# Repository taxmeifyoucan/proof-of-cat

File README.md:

**[ENG](README.md) | [CAT](README_cat.md)**

# Proof-of-Cat: Cat as an entropy generator

Proof-of-Cat is a novel approach to generating randomness for cryptographic systems, utilizing the inherent unpredictability and entropy of domestic felines, also known as cats.

To learn more, read the **[CatPaper](./proofofcat.pdf)** and check the **Catropy [docs](./docs.md)**. 

## Catropy

_Catropy_ is a CRNG (Cat Random Number Generator) designed as an implementation of Proof-of-Cat. Research and development of this device was intented for participation in [Ethereum KZG Ceremony](https://github.com/ethereum/kzg-ceremony) and supported by EF grant. Read the [blog](./blog.md) about how Catropy uses cats to secure Ethereum.

It's a basically toy which can generate randomness from its movement. The circuit board is a microcontroller with wifi and battery which enables to use the device fully remotely. To learn more about hardware design and usage, look into the [documentation](./docs.md). 

The toy is not just a circuit board. It comes in hand-made knitted ball which protects the electronics and provides soft experience. It was demonstrated that it works well not just with [cats](https://twitter.com/i/status/1632706164231118848), [but also core devs](https://twitter.com/liamihorne/status/1617974952413761536). Various versions and color combinations are available. Check example pictures below. 

Device can be used to contribute to the KZG Ceremony but it is not its sole purpose. The Catropy software enables you to use it for generating entropy for anything which needs it. But the device is general purpose and you can reprogram it to utilize the microctroller however you want. For example, another use case being developed is for using the device for medical diagnostic of patients based on tracking their movement and its changes. 

## Get a Catropy device

Catropy was designed as an open-source device with no profit incentives. You can build the device by yourself but if you would like purchase one, you can do it by donating to a [cat shelter in Catalonia](https://www.eljardinetdelsgats.org). Based on donation of minumum 0.02ETH, we will reward you with a fully featured Catropy toy. 

And if you are a member of Protocol Guild, the toy completely on us! 

### Donation

Donations are handled by us, converted to fiat and physically donated to [El Jardinet dels Gats](https://www.eljardinetdelsgats.org), a non-profit helping cats which was also involved testing the Catropy toy. In case we receive high number of donations (0.5ETH+), it will be split between Jardinet and another [local organization](https://www.degats.org/) with multiple colonies. The official donation address is catropy.eth (0x543cbBD2bf6f6eC71254E75b7FEAbb222B143343). All funds on this address will be donated to help with expenses in the shelter - food, materials, veterinary checks, treatement and vaccinations. 

### Shipping 

You can pickup Catropy personally during **EthPrague** conference or rest of the year in [Paralelní Polis](https://goo.gl/maps/rJfCFSxNbkSRXrLw9) or in Barcelona. 

Otherwise we can ship it to your address. Just add shipping fee to your donation, you can use a [shipping estimate calculator](https://coolparcel.com/). (0.5kg package, shipping from Czech republic, 17001). Feel free to reach out if you are not sure, we can ship it first and let you know the exact cost. 

### How to

Step by step, this is how you get your device: 

- Donate minimum of 0.02ETH (around 30EUR) to catropy.eth or 0x543cbBD2bf6f6eC71254E75b7FEAbb222B143343. You can use mainnet, Arbitrum, Optimism, Polygon, Gnosis chain or Aztec (zk.money, address is @catropy). For donating over other chains, reach out to us. 
- Choose a color combination. Balls come in various colors, we prepared gray with colorful ETH logo, pink with white logo and blue with yellow. Check pictures below and more in [assets directory](https://github.com/taxmeifyoucan/proof-of-cat/tree/gh-pages/src/assets). If you wish your own color combination, feel free to write us but note it might take few extra days before shipping. 
- Send us an email to meow@proofof.cat with your shipping details (your address or pickup option), chosen color and sign it with the address you sent donation from. Signing message with a wallet is easy, you can use a tool like [MyCrypto](https://app.mycrypto.com/sign-message). If you are a Protocol Guild member, sign it using your address PG or just contact us to verify it's really you. 
- Embrace the chaos 

## Contact

For support, orders and any kind of questions, please contact us at meow@proofof.cat

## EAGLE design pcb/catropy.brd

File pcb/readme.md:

# Catropy PCB

Schematics for the Catropy board. Files in this directory contain all sources for Catropy hardware and can be opened using Eagle or similar software.

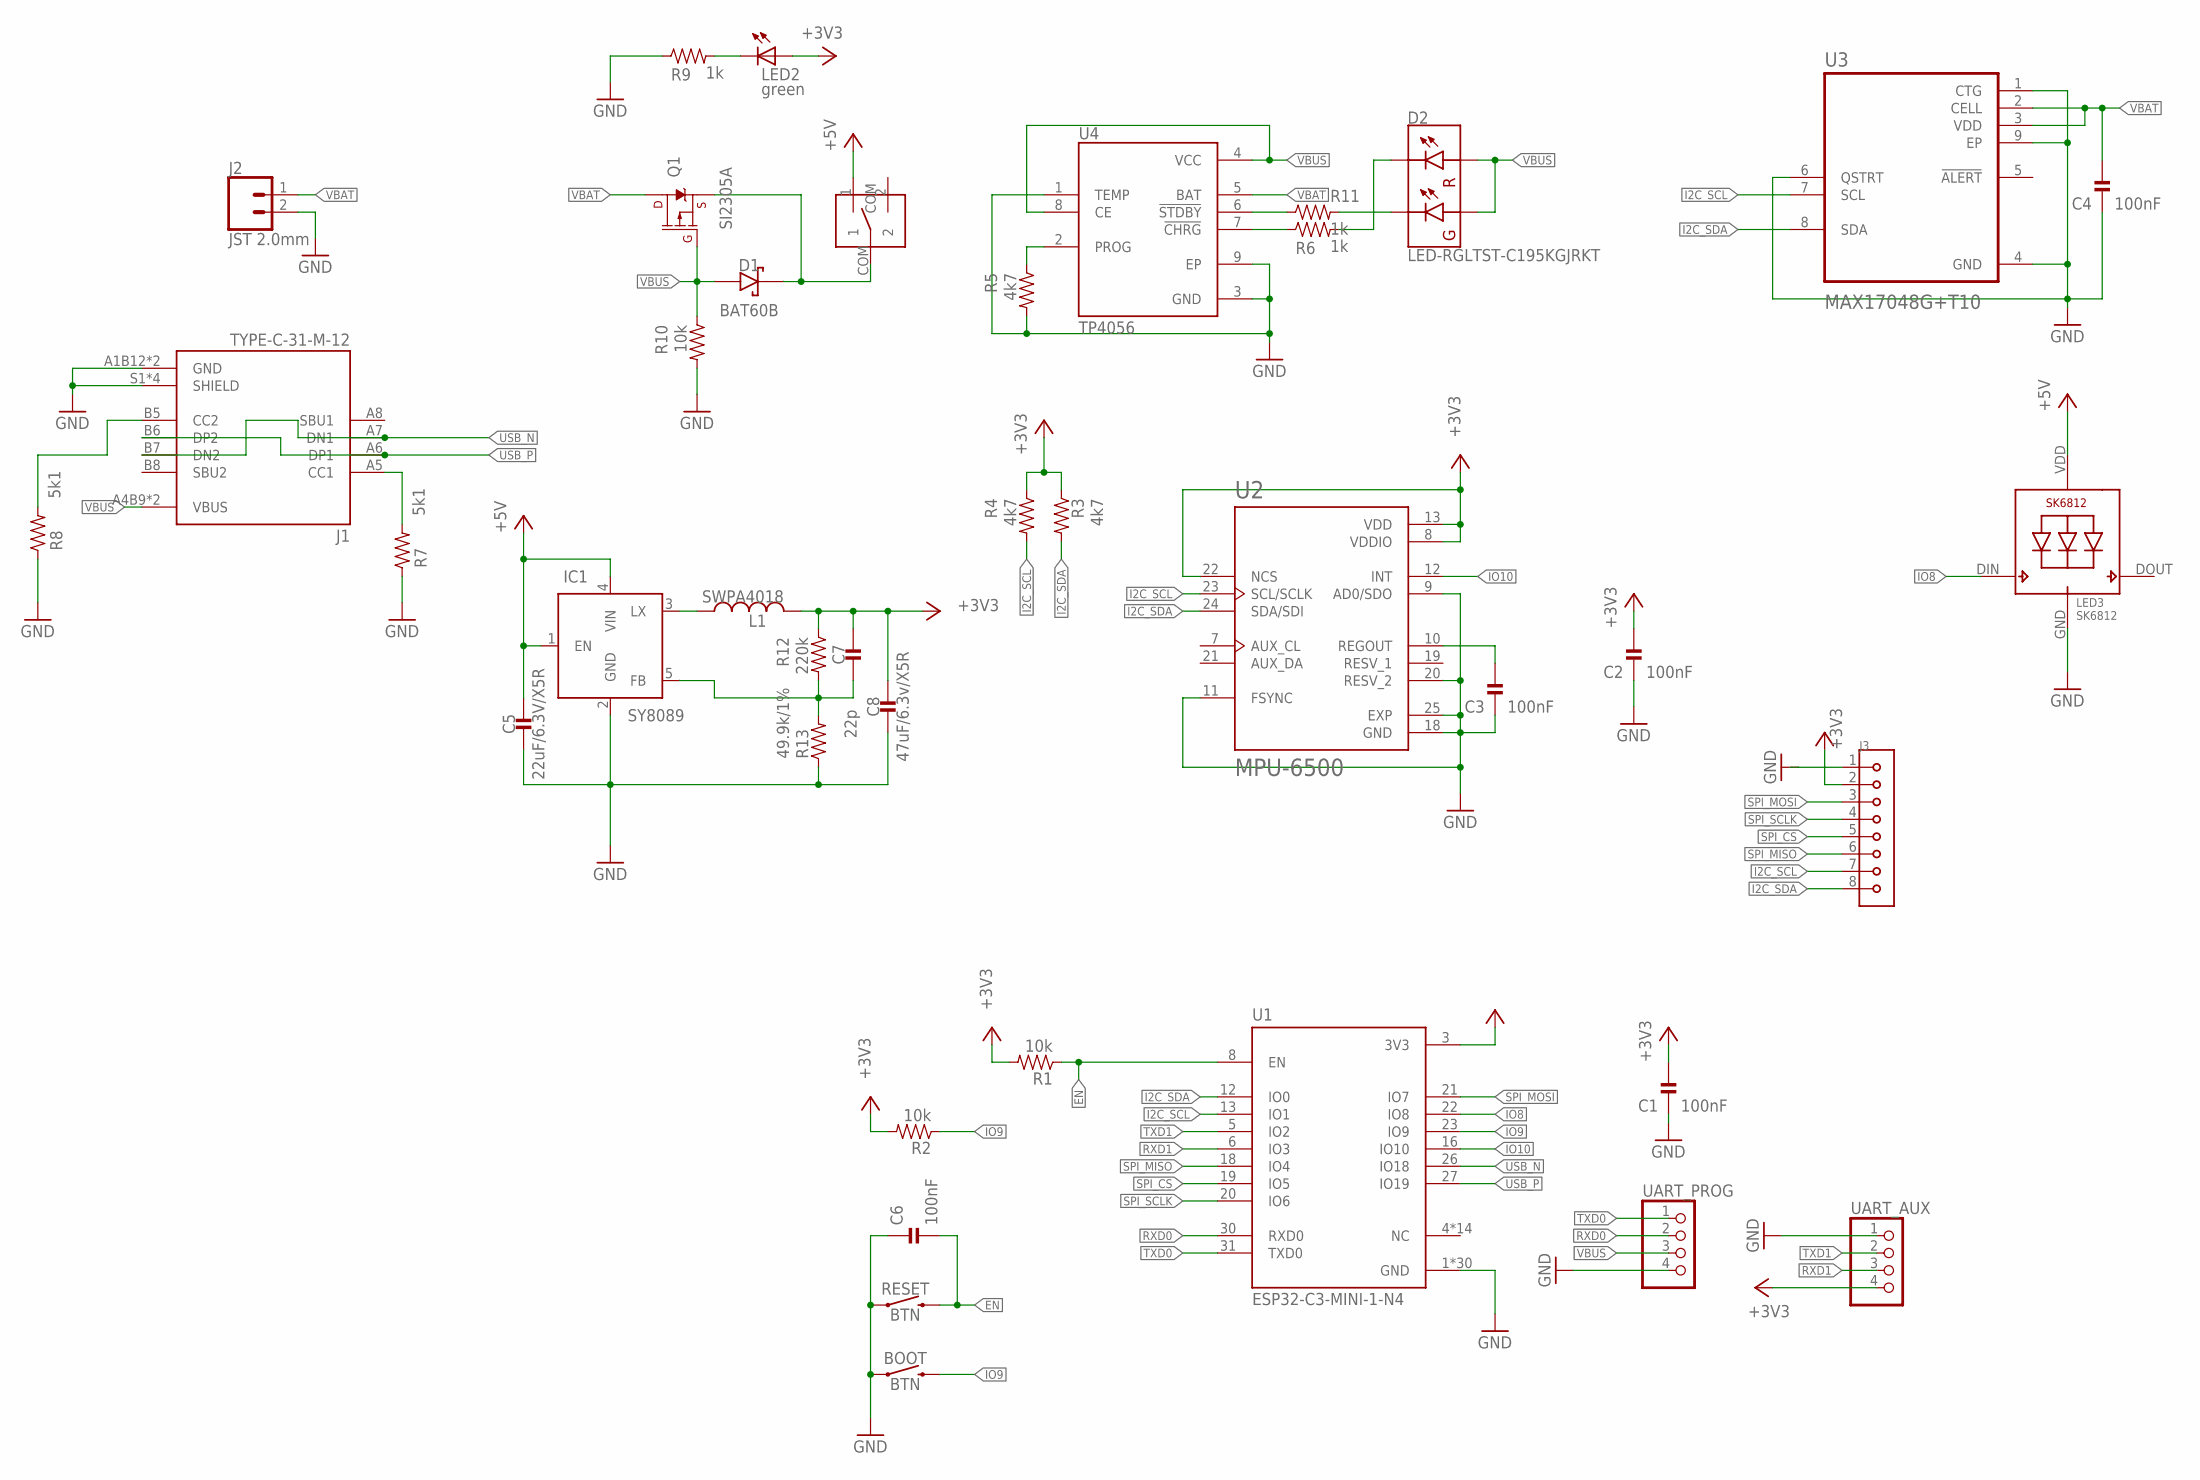
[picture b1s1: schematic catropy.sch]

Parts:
BOOT: BTN; TACTILE_SWITCH_SMD_6.0X3.5MM; LCSC_PART C118141
C1, C2, C3, C4, C6: 100nF; 0402_CAP
C5: 22uF/6.3V/X5R; 0603_CAP
C7: 22p; 0402_CAP
C8: 47uF/6.3v/X5R; 0805_CAP
D1: BAT60B; SOD323; LCSC_PART C22638
D2: LED-RGLTST-C195KGJRKT; LTST-C195KGJRKT; LCSC_PART C125104
IC1: SY8089; SOT23-5; LCSC_PART C78988
J1: TYPE-C-31-M-12; HRO_TYPE-C-31-M-12; LCSC_PART C165948
J2: JST 2.0mm; JST-2-SMD; LCSC_PART C3029440
J3: SM08B-SRSS-TB(LF)(SN); JST_SM08B-SRSS-TB(LF)(SN); LCSC_PART C160407
L1: SWPA4018; SWPA40XX; LCSC_PART C50543
LED2: green; CHIPLED_0603; LCSC_PART C72043
LED3: SK6812; LED_EC3210R; LCSC_PART C2890041
Q1: SI2305A; SOT23-3; LCSC_PART C347488
R1, R2, R10: 10k; 0402_RES
R3, R4, R5: 4k7; 0402_RES
R6, R9, R11: 1k; 0402_RES
R7, R8: 5k1; 0402_RES
R12: 220k; 0402_RES
R13: 49.9k/1%; 0402_RES; LCSC_PART C208898
RESET: BTN; TACTILE_SWITCH_SMD_6.0X3.5MM; LCSC_PART C118141
U1: ESP32-C3-MINI-1-N4; XCVR_ESP32-C3-MINI-1-N4; LCSC_PART C2838502
U2: MPU-6500; QFN40P300X300X95-25N; LCSC_PART C50278
U3: MAX17048G+T10; SON50P200X200X80-9N; LCSC_PART C2682616
U4: TP4056; SOP127P600X175-9N
U$1: SK12D07VG4; LCSC_PART C393937
UART_AUX: PINHD-1X4; 1X04
UART_PROG: PINHD-1X4; 1X04

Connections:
5V_AUX: D1.P$1 (CATHODE), Q1.2 (S), U$1.COM
+3V3: C1.2, C2.2, C7.1, C8.P$1 (1), J3.2, L1.P$2 (2), LED2.A, R1.2, R2.2, R3.1, R4.1, R12.1, U1.3 (3V3), U2.8 (VDDIO), U2.13 (VDD), U2.22 (NCS), UART_AUX.4
+5V: C5.1, IC1.1 (EN), IC1.4 (VIN), LED3.VDD, U$1.1
EN: C6.2, R1.1, RESET.2, U1.8 (EN)
GND: BOOT.1, C1.1, C2.1, C3.1, C4.1, C5.2, C6.1, C8.P$2 (2), IC1.2 (GND), J1.A1B12 (GND), J1.B1A12 (GND), J1.S1 (SHIELD), J1.S2 (SHIELD), J1.S3 (SHIELD), J1.S4 (SHIELD), J2.2 (1), J3.1, LED3.GND, R5.2, R7.1, R8.1, R9.1, R10.2, R13.1, RESET.1, U1.1 (GND), U1.2 (GND), U1.11 (GND), U1.14 (GND), U1.36 (GND), U1.37 (GND), U1.38 (GND), U1.39 (GND), U1.40 (GND), U1.41 (GND), U1.42 (GND), U1.43 (GND), U1.44 (GND), U1.45 (GND), U1.46 (GND), U1.47 (GND), U1.48 (GND), U1.49_1 (GND), U1.49_2 (GND), U1.49_3 (GND), U1.49_4 (GND), U1.49_5 (GND), U1.49_6 (GND), U1.49_7 (GND), U1.49_8 (GND), U1.49_9 (GND), U1.50 (GND), U1.51 (GND), U1.52 (GND), U1.53 (GND), U2.9 (AD0/SDO), U2.11 (FSYNC), U2.18 (GND), U2.20 (RESV_2), U2.25 (EXP), U3.1 (CTG), U3.4 (GND), U3.6 (QSTRT), U3.9 (EP), U4.1 (TEMP), U4.3 (GND), U4.9 (EP), UART_AUX.1, UART_PROG.4
I2C_SCL: J3.7, R4.2, U1.13 (IO1), U2.23 (SCL/SCLK), U3.7 (SCL)
I2C_SDA: J3.8, R3.2, U1.12 (IO0), U2.24 (SDA/SDI), U3.8 (SDA)
IO8: LED3.DIN (DI), U1.22 (IO8)
IO9: BOOT.2, R2.1, U1.23 (IO9)
IO10: U1.16 (IO10), U2.12 (INT)
unnamed: R5.1, U4.2 (PROG)
unnamed: R6.1, U4.7 (!CHRG)
unnamed: J1.A5 (CC1), R7.2
unnamed: R11.1, U4.6 (!STDBY)
unnamed: D2.P$3 (GC), R11.2
unnamed: C7.2, IC1.5 (FB), R12.2, R13.2
unnamed: C3.2, U2.10 (REGOUT)
unnamed: IC1.3 (LX), L1.P$1 (1)
unnamed: D2.P$4 (RC), R6.2
unnamed: LED2.C, R9.2
unnamed: J1.B5 (CC2), R8.2
RXD0: U1.30 (RXD0), UART_PROG.2
RXD1: U1.6 (IO3), UART_AUX.3
SPI_CS: J3.5, U1.19 (IO5)
SPI_MISO: J3.6, U1.18 (IO4)
SPI_MOSI: J3.3, U1.21 (IO7)
SPI_SCLK: J3.4, U1.20 (IO6)
TXD0: U1.31 (TXD0), UART_PROG.1
TXD1: U1.5 (IO2), UART_AUX.2
USB_N: J1.A7 (DN1), J1.B7 (DN2), U1.26 (IO18)
USB_P: J1.A6 (DP1), J1.B6 (DP2), U1.27 (IO19)
VBAT: C4.2, J2.1 (2), Q1.3 (D), U3.2 (CELL), U3.3 (VDD), U4.5 (BAT)
VBUS: D1.P$2 (ANODE), D2.P$1 (GA), D2.P$2 (RA), J1.A4B9 (VBUS), J1.B4A9 (VBUS), Q1.1 (G), R10.1, U4.4 (VCC), U4.8 (CE), UART_PROG.3

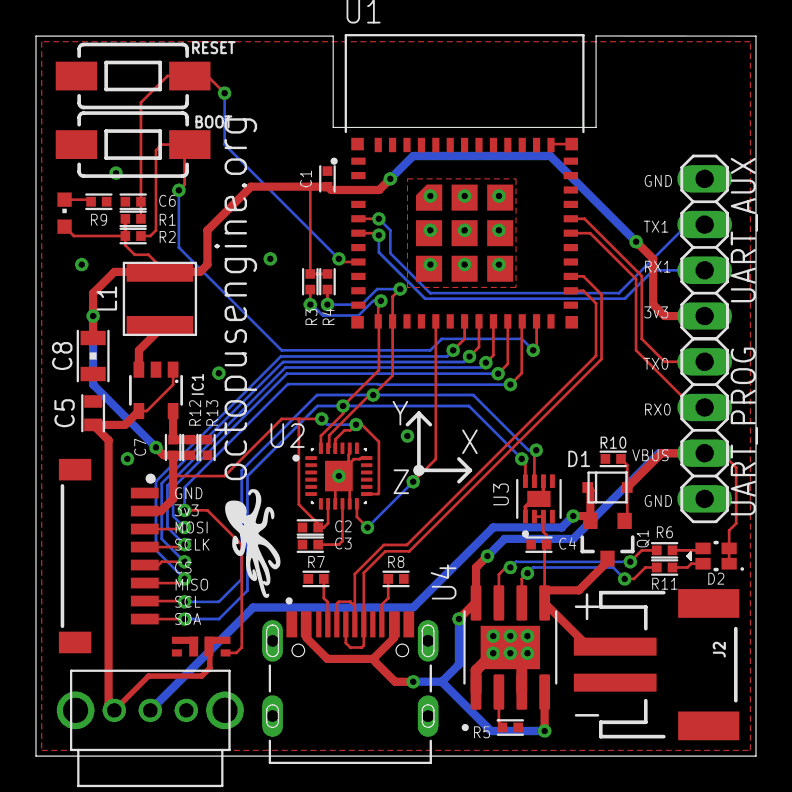
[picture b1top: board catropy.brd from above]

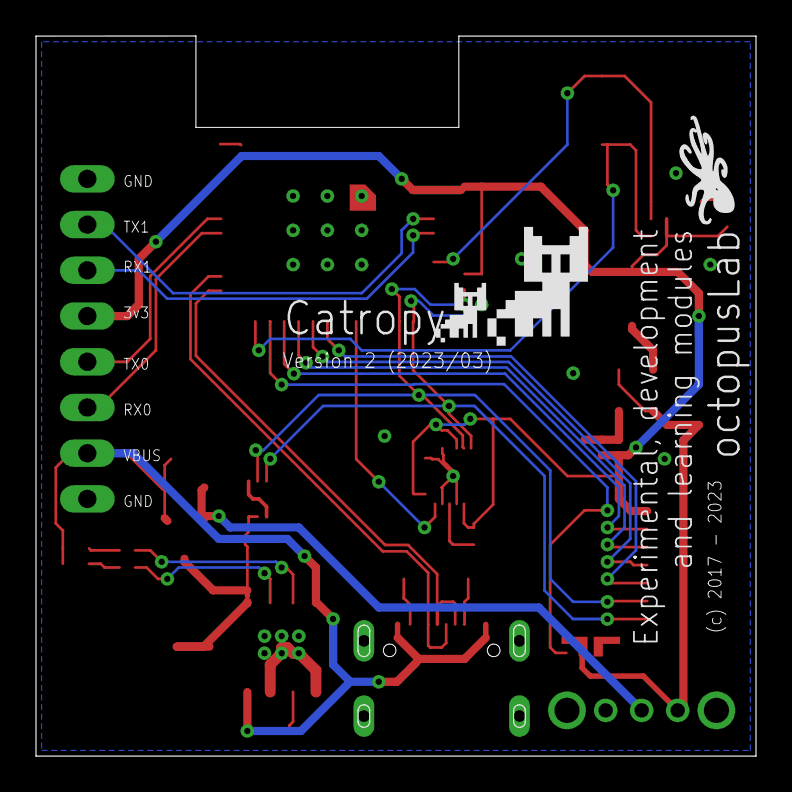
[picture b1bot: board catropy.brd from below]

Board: 2 copper layers, 40.0 x 40.0 mm, 44 parts (2 on the bottom side), 33 nets.

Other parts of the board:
U$2: OCTOPUSLAB
U$3: OCTOPUSENGINE
U$4: CATROPY_20
U$5: CATROPY_10

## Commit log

2022-11-18 Create poc web
2022-11-18 gh-pages
2022-11-18 Add gh pages content
2022-11-18 Create CNAME
2023-01-09 Add cat paper, pics
2023-01-09 update the cat paper
2023-02-02 Update readme, add pictures
2023-02-02 add favicon
2023-02-19 clean repo
2023-02-22 add docs
2023-02-23 improve docs
2023-02-23 IP error
2023-02-23 clean repo and code
2023-02-23 add pics
2023-02-24 refactoring: and new gyro lib
2023-02-24 refactoring: lib, tests and config (wifi.json)
2023-02-24 refactoring: with json setup file
2023-02-24 fix shuffle function
2023-02-24 move to lib/entropy_lib
2023-02-24 add RGB led, refactoring entropy lib, clean up
2023-02-25 Handling LEDs
2023-02-25 Wifi error handling, remove old lib
2023-02-25 Add led gyro test
2023-02-26 add a separate library for hw components
2023-02-26 refactoring - hw components
2023-02-27 Docs on KZG contributions, status LEDs
2023-03-15 update docs
2023-04-18 FIX root entropy endpoint return correct headers
2023-04-18 FIX: strip \n from payload in entrypy base64 encoded string
2023-04-18 Prolong wifi retries, add yellow RGB led for connecting status
2023-04-19 add blog writeup
2023-04-24 PCB: Added BOM and CPL for power switch
2023-04-24 Sync version v2r2 of PCB
2023-04-24 PCB: Some TODO
2023-04-24 update docs and blog
2023-05-09 update blogpost
2023-05-09 add jekyll web version
2025-12-22 add cat
2025-12-22 update translation
2025-12-22 fix link

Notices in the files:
parts and their libraries:
octopus: (c) 2017 - 2023
SparkFun-Switches: Licensing: Creative Commons ShareAlike 4.0 International - https://creativecommons.org/licenses/by-sa/4.0
